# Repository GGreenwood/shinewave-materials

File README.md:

This repository contains supporting materials for the upcoming tasks to be completed before the Shinewave Kickstarter.

Shinewave is a project aimed at competitive Super Smash Bros players that seeks to modify and improve GameCube controllers with programmable LEDs and various USB functionalities. The electronics and firmware have already been prototyped and are showcased on my blog at [Electric Exploits](http://electricexploits.net/).

However, official clear controller backs(necessary to see the LEDs) are difficult to find, tend to be in used condition, and cost about $40 each. Therefore, I hope to produce my own replica of the official injection molded backs.

Since I will have full control over the new model, I hope to include several modifications that will make assembly easier and allow for easy USB connections.

# Contents

| Folder                   | Contents                                          |
| ------------------------ | ------------------------------------------------- |
| `./controller-model`     | Rough 3D scan of a GameCube controller back       |
| `./shinewave-board/main` | Schematics and board for the main Shinewave PCB   |
| `./shinewave-board/leds` | Schematics and board for each LED                 |

# Todo

## Produce injection molded clear backs

It is the most important to produce a piece that mates well with the official top half of the shell, so that the two pieces join together seamlessly. The controller has a lot of odd curves in its geometry, so this may be difficult.

I tried taking a 3D scan of the controller back with a NextEngine desktop scanner, but the scan quality wasn't too great. I uploaded it anyways, because it may be a good place to start.

Additionally, there are several modifications that I would like to make to the base model.

## PCB mounting points

As it stands, I have been either hot gluing parts into the case, or letting wire tension keep them in place. This works fine for small scales of production, but would error-prone in larger quantities.

I would like to include some mounting mechanism for the main PCB, and each of the five LED PCBs. I'm not sure what kind of mounting mechanism would be injection-molding friendly.

In the album below, I've marked the approximate mounting point locations. The LEDs are marked by X's, while the Shinewave PCB is marked by the rectangle on the back. Additionally, the USB port is the filled inner rectangle on the back.

[PCB Mounting points](http://imgur.com/a/13wrS)

## USB access

In order to use the controller as a USB joystick, update the firmware, or modify the LEDs without disassembling the controller, a microUSB port in the back would be necessary. The port would be orthogonal(probably) to the main Shinewave PCB, which will have a right-angle microUSB connector, similar to [this](http://www.mouser.com/ProductDetail/Hirose-Connector/ZX80-B-5S/?qs=XQjbzJWzFPUrLcP5tM9rJg%3D%3D).

## Misc

Finally, I would like to get an opinion on the following tasks

 * Choosing good board to board connectors, and finding a source for the custom length wires
 * Finding a medium-run manufacturer to do production and PCB assembly, and getting a quote

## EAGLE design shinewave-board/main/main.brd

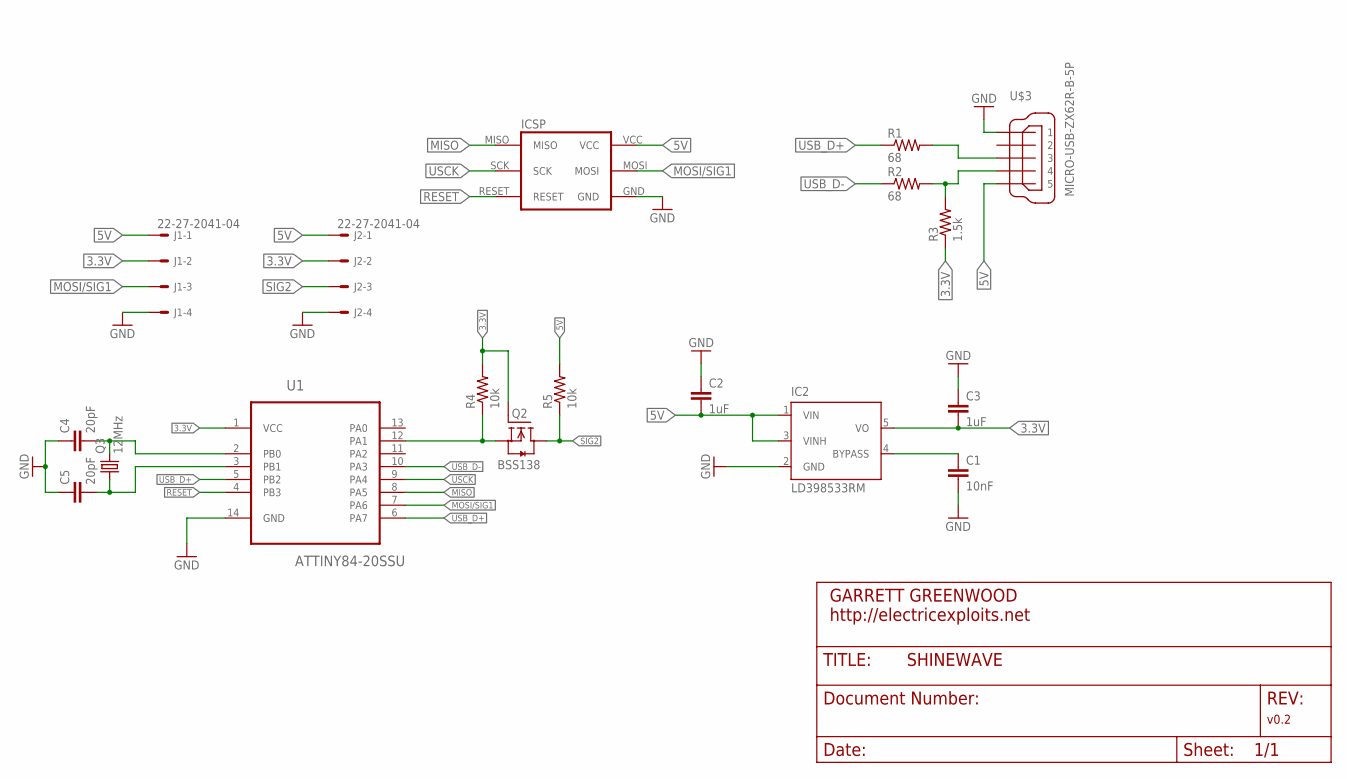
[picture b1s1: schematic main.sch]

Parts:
C1: 10nF; C0603
C2, C3: 1uF; C0603
C4, C5: 20pF; C0603
IC2: LD398533RM; SOT23-5L
J1, J2: 22-27-2041-04; 6410-04
Q2: BSS138; SOT23
Q3: 12MHz; CTS406
R1, R2: 68; R0603
R3: 1.5k; R0603
R4, R5: 10k; R0603
U1: ATTINY84-20SSU; SOIC127P600X175-14N
U$1: ICSP_POGO_INTERFACE; ICSP_SMD
U$3: MICRO-USB-ZX62R-B-5P; ZX62R-B-5P

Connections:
3.3V: C3.2, IC2.5 (VO), J1.2, J2.2, Q2.1 (G), R3.1, R4.2, U1.1 (VCC)
5V: C2.2, IC2.1 (VIN), IC2.3 (VINH), J1.1, J2.1, R5.2, U$1.VCC, U$3.5
GND: C1.2, C2.1, C3.1, C4.1, C5.1, IC2.2 (GND), J1.4, J2.4, U1.14 (GND), U$1.GND, U$3.1
MISO: U1.8 (PA5), U$1.MISO
MOSI/SIG1: J1.3, U1.7 (PA6), U$1.MOSI
unnamed: Q2.2 (S), R4.1, U1.12 (PA1)
unnamed: C1.1, IC2.4 (BYPASS)
unnamed: R1.2, U$3.3
unnamed: R2.2, R3.2, U$3.4
RESET: U1.4 (PB3), U$1.RESET
SIG2: J2.3, Q2.3 (D), R5.1
USB_D+: R1.1, U1.5 (PB2), U1.6 (PA7)
USB_D-: R2.1, U1.10 (PA3)
USCK: U1.9 (PA4), U$1.SCK
XTAL1: C4.2, Q3.3 (2), U1.2 (PB0)
XTAL2: C5.2, Q3.1, U1.3 (PB1)

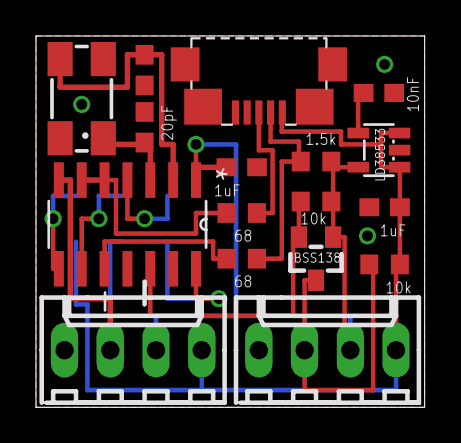
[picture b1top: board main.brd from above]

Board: 2 copper layers, 21.6 x 20.6 mm, 18 parts (0 on the bottom side), 16 nets.

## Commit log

2016-04-10 Added download link to controller back scan
2016-04-10 Added main shinewave board and schematics
2016-04-11 Added LED board and schematics
2016-04-11 first README
2016-04-11 fixed table formatting
2016-04-11 removed readme in wrong directory
2016-04-11 Added mounting point images

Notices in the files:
parts and their libraries:
m-pad-2.1: License : GNU General Public License version 2 (see bottom)
